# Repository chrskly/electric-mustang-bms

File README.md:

# Electric Mustang BMS

This repo contains the hardware design and software for the custom BMS for my EV conversion project.

## Overview

The BMS is always on.

The battery is made up of one or two BMW PHEV battery packs.

Each battery pack has a positive and negative contactor which are activated by
either the ignition key or when charging.

The BMS is able to inhibit the closing of the contactors in each battery pack
individually.

The car will also have precharge and main contactors in the HVJB. These are
controlled by the inverter.

## Compiling/Installing

### Building the BMS code

```
cd src/build
cmake ../
make
```

### Building the test framework code

```
cd test/build
cmake ../
make
```

## High Voltage wiring

```
       +--------- fuse --- batt1-pos-cont ---+
       |                                     |
       |     +--- fuse --- batt2-pos-cont ---+
       |     |                               |
       |     |                               +--- precharge ---+
batt1 ---   --- batt2                        |                 |
       -     -                               +--- main-cont ---+--->
       |     |
       |     |
       |     +------------ batt2-neg-cont ---+---- neg-cont ------->
       |                                     |
       +------------------ batt1-neg-cont ---+
```

* batt1-pos-cont, batt1-neg-cont, batt2-pos-cont, and batt2-neg-cont are
  contactors located inside the respective battery boxes. They are powered by
  ignition on or by charging on.
* The power for the battery contactors passes through the normally closed side
  of a relay. The BMS can inhibit the closing of the contactors in either
  battery separately by closing the respective relay.
* The inverter controls the precharge, main and neg contactors.

## State machine

### States

* standby
* drive
* batteryHeating
* charging
* batteryEmpty
* overTempFault
* illegalStateTransitionFault
* criticalFault

### Events

| Event | Description |
| --- | --- |
| E_TOO_HOT | The battery is overheating. |
| E_TOO_COLD_TO_CHARGE | The battery temperature is too cold. |
| E_TEMPERATURE_OK | The battery temperature is in an OK range. |
| E_BATTERY_EMPTY | The battery has one or more 'empty' cells. |
| E_BATTERY_NOT_EMPTY | The battery charge is in an OK range. |
| E_BATTERY_FULL | The battery has one or more 'full' cells. |
| E_PACKS_IMBALANCED | The voltage of the two packs differ. |
| E_PACKS_NOT_IMBALANCED | The voltage of the two packs are the same. |
| E_IGNITION_ON | the ignition has been turned on. |
| E_IGNITION_OFF | the ignition has been turned off. |
| E_CHARGING_INITIATED | charging has been initiated. |
| E_CHARGING_TERMINATED | charging has been stopped. |
| E_MODULE_UNRESPONSIVE | One or battery modules are not reporting in to the BMS. |
| E_MODULES_ALL_RESPONSIVE | All battery modules are reporting in to the BMS. |
| E_SHUNT_UNRESPONSIVE | The ISA shunt is not transmitting updates. |
| E_SHUNT_RESPONSIVE | The ISA shunt is transmitting updates. |
| E_DEAD_CELL | On of the cells has failed (voltage too low) |

## Functionality

### General
* Monitor voltage of every cell in the pack.
* Provide SoC estimate (based on shunt data)
* Provide range estimate [TODO]

### Charging
* Provide max charge current value based on temperature and SoC
* Protect cells by disallowing charging at high/low temperatures
* Disallow charging when battery is full

### Driving
* Protect cells by disallowing driving at high temperatures
* Disallow driving when battery is empty

### Paralleling packs

I will be using two BMW PHEV packs connected in parallel. This introduces some
additional complications.

#### Packs Getting Out of Sync

When the car is off, the packs will be disconnected from each other as well as
from the rest of the car. There is the possibility that the packs will drift a
little apart from each other in terms of their voltage. For example, they'll be
placed in different locations in the car, so will experience slightly different
thermals.

* Provide protection for issues relating to paralleling packs. Deny contactor
  close when pack voltages (not cell voltages) differ by more than a certain
  number of mV. Instead, when going into drive mode, only close the
  contactors for the pack with the highest voltage and, when going into charge
  mode, only close the contactors for the pack with the lowest voltage. Car
  will still be drivable and full battery capacity will still be usable (by
  turning ignition off and on again).
* When driving on a subset of packs, allow contactors to close when the pack
  voltages get back into alignment.
* When charging on a subset of packs, allow contactors to close when the pack
  voltages get back into alignment.

#### Dead Cell Detection

One of the risks associated with paralleling packs is if a cell in one of the
packs fails in a closed state, then the voltage of that pack drops. You'll then
get a large, uncontrolled current flow from the 'good' pack to the 'bad' pack.

To attempt to guard against this, this BMS implements dead cell detection. If
any cell is found to have a voltage reading under DEAD_CELL_VOLTAGE that pack is
uncontitionally isolated by inhibiting contactor close (opening the contactors)
for the pack.

If we only have one pack:
  > Warn that dead cell has been detected, but take no other action

If we have multiple packs:
  Idle

### ISA Shunt
* Read CAN messages from shunt to track of voltage, current, kwh
* Reset shunt counters when battery has been charged to 100%

## Connections

1. CAN port connected to main CAN bus.
2. CAN port connected to front battery CAN bus.
3. CAN port connected to rear battery CAN bus.
4. Low side switch for front battery contactors. Contactors are actually
   controlled by inverter, but BMS can override.
5. Low side switch for rear battery contactors. Contactors are actually
   controlled by inverter, but BMS can override.
6. Low side switch to turn on battery heater.
7. IGNITION_ON input signal
8. CHARGE_ENABLE input signal
9. CHARGE_INHIBIT output signal
10. DRIVE_INHIBIT output signal

## Pinout

```
|                                               |
| A7 A8 A9 A10 A11 A12     B1  B2  B3  B4 B5 B6 |
| A6 A5 A4 A3  A2  A1      B12 B11 B10 B9 B8 B7 |
+-----------------------------------------------+
```

### BMS

- A1  : GPIO_13 : IN_3  / BATT1_CONTACTOR_FEEDBACK
- A2  : GPIO_11 : IN_1  / POS_CONTACTOR_FEEDBACK
- A3  : GPIO_9  : IN_X  / CHARGE_ENABLE_IN
- A4  : GPIO_6  : OUT_3 / DRIVE_INHIBIT
- A5  : GPIO_4  : OUT_1 / CHARGE_INHIBIT
- A6  : GPIO_3  : OUT_X / BATT_2_INHIBIT
- A7  : GPIO_2  : OUT_X / BATT_1_INHIBIT
- A8  : GPIO_5  : OUT_2 / HEATER_ENABLE
- A9  : GPIO_7  : OUT_4
- A10 : GPIO_10 : IN_X  / IGNITION_ON_IN
- A11 : GPIO_12 : IN_2  / NEG_CONTACTOR_FEEDBACK
- A12 : GPIO_14 : IN_4  / BATT2_CONTACTOR_FEEDBACK

- B1 : BATT_2_CAN_H
- B2 : BATT_1_CAN_H
- B3 : MAIN_CAN_H
- B4 : GND
- B5 : 12V
- B6 : GND
- B7 : 5V
- B8 : 5V
- B9 : GND
- B10 : MAIN_CAN_L
- B11 : BATT_1_CAN_L
- B12 : BATT_2_CAN_L

### Tester

- A1  : GPIO_13 : IN_3  / DRIVE_INHIBIT
- A2  : GPIO_11 : IN_1  / CHARGE_INHIBIT
- A3  : GPIO_9  : IN_X  / HEATER_ENABLE
- A4  : GPIO_6  : OUT_3 / 
- A5  : GPIO_4  : OUT_1 / CHARGE_ENABLE
- A6  : GPIO_3  : OUT_X / 
- A7  : GPIO_2  : OUT_X / IGNITION_ON
- A8  : GPIO_5  : OUT_2 / 
- A9  : GPIO_7  : OUT_4 /
- A10 : GPIO_10 : IN_X  / 
- A11 : GPIO_12 : IN_2  / BATT_2_INHIBIT
- A12 : GPIO_14 : IN_4  / BATT_1_INHIBIT

- B1 : BATT_2_CAN_H
- B2 : BATT_1_CAN_H
- B3 : MAIN_CAN_H
- B4 : GND
- B5 : 12V
- B6 : GND
- B7 : 5V
- B8 : 5V
- B9 : GND
- B10 : MAIN_CAN_L
- B11 : BATT_1_CAN_L
- B12 : BATT_2_CAN_L

## CAN messages consumed by BMS

- Shunt messages - kWh, Ah, current, voltage (0x521 - 0x528)

## CAN messages produced by BMS

- Shunt reset message
- Min battery voltage (0x351)
- Max battery voltage (0x351)
- Max charge current (0x351)
- Max discharge current (0x351) [ not implemented yet ]
- BMS state - standby, drive, ... (0x352)
- Errors flags - internalError, packsImbalanced, shuntIsDead, illegalStateTransition (0x352)
- Status flags - inhibitCharge, inhibitDrive, heaterEnabled, ignitionOn, chargeEnable, disableRegen (0x352)
- Charge inhibit reason - none, too hot, too cold, battery full, battery empty, charging, illegal state transition (0x352)
- Drive inhibit reason - as above (0x352)
- Welding bits - posContactorWelded, negContactorWelded, batt1ContactorWelded, batt2ContactorWelded (0x352)
- Module liveness (0x353)
- SoC (0x355)
- Battery voltage - as reported by BMS and as reported by shunt (0x356)
- Battery current - as reported by shunt (0x356)
- Battery highest temperature (0x356)
- High cell voltage alarm, warn (0x35A)
- Low cell voltage alarm, warn (0x35A)
- High temp alarm, warn (0x35A)
- Low temp alarm, warn (0x35A) [ not implemented yet ]
- Cell delta alarm (0x35A)

## Configurables

1. minCellVoltage - disallow drive when cell voltage at or below this level.
2. maxCellVoltage - disallow charge when cell voltage at or above this level.
3. maxPackVoltageDelta - max allowed difference in voltage between packs. Above
   this, contactors will not be allowed to close.
4. minChargeTemp - disallow charging at or below this temperature.

## Charging

When in charge mode the BMS will emit a maximum allowed charge current in the
0x351 CAN message. The chargers will listen for this and adjust their request
accordingly.

### Temperature derating

There is a minimum temperature below which we must not charge. So we disallow
charging at or below -10°C.

Above the minimum, we need to limit the charge current. So we ramp up the
allowed current as temperature increases. This is between -10°C and 15°C.

In the 'happy temperature' range (between 15°C and 35°C) we allow the full 125A
(delivered by a 50kw charger). However, if the temperature of the pack increases
by more than 1°C per minute, derate the charge current by 10% for every degree
over.

Above 35°C, we ramp back down the current. We also derate based on temperature
increase on top of that.

It looks something like this.

```
current
   ^
   |
   |                    /----------------------\
   |                  /                         \
   |                /                            \
   |              /                               \
   |            /                                  \
   |          /                                     \
   |        /                                        \
   |      /                                           \
   |    /                                              \
   |  /                                                 \
   +-+------------------+---------------------+----------+----> temperature
    -10°               15°C                  35°C       40°C
```

### SoC derating

TODO : just go slow about 80%?

## Welded Contactor Detection

There are four inputs on the BMS for welded contactor detection.

1. HVJB positive contactor
2. HVJB negative contactor
3. Battery 1 contactors
4. Battery 2 contactors

There are four bits in the status CAN message (0x352) for reporting
welded contactors (one bit for each of the above).

The weld detection only runs when the car is in standby mode (the
only time it makes sense).

Both the positive and negative contactors in the HVJB have dedicated
feedback inputs. The switched side of the auxiliary side of the
contactor should be fed into this input. I.e., feed it 12V when the
contactor is closed.

The battery contactors just have one input each. We can use diodes to
report if either of the battery contactors (positive or negative) are
welded.

## To Do

- [x] Fetch SoC from shunt and store in memory
- [x] Broadcast BMS mode
- [x] CHARGE_ENABLE input
- [x] IGNITION_ON input
- [x] DRIVE_INHIBIT output
- [ ] Use other core for comms?
- [x] Implement balancing
- [x] Implement watchdog
- [ ] On startup, properly detect the state we should start in and immediately switch to that state
- [x] Emulate SimpBMS output CAN messages
- [x] Reset ISA Shunt when battery charged to 100%
- [x] ISA shunt heartbeat
- [x] Warn/alarm flags
- [x] Warn when modules are missing
- [ ] Deal with scenario when one pack is full and one pack is empty
- [x] Communication error bit(s)
- [x] Counter for failed CAN messages received (checksum?), sent
- [x] enable/disable regen bit
- [x] inhibit function naming confusing
- [x] charge_inhibit_reason can msg
- [x] drive_inhibit_reason can msg
- [x] transmit module liveness over can   
- [x] welded contactor detection
- [ ] manual battery pre-heat
- [x] Disallow charging when BMS cannot 'see' shunt
- [ ] Provide range estimate
- [ ] Save certain values to flash (error counters, state?, )
- [ ] Dead cell detection

## Credits

This project uses the [adamczykpiotr/pico-mcp2515](https://github.com/adamczykpiotr/pico-mcp2515) 
library for CAN communication.

The [Tom-evnut/BMWPhevBMS](https://github.com/Tom-evnut/BMWPhevBMS) project was
used as a reference for how to communicate with this battery pack.

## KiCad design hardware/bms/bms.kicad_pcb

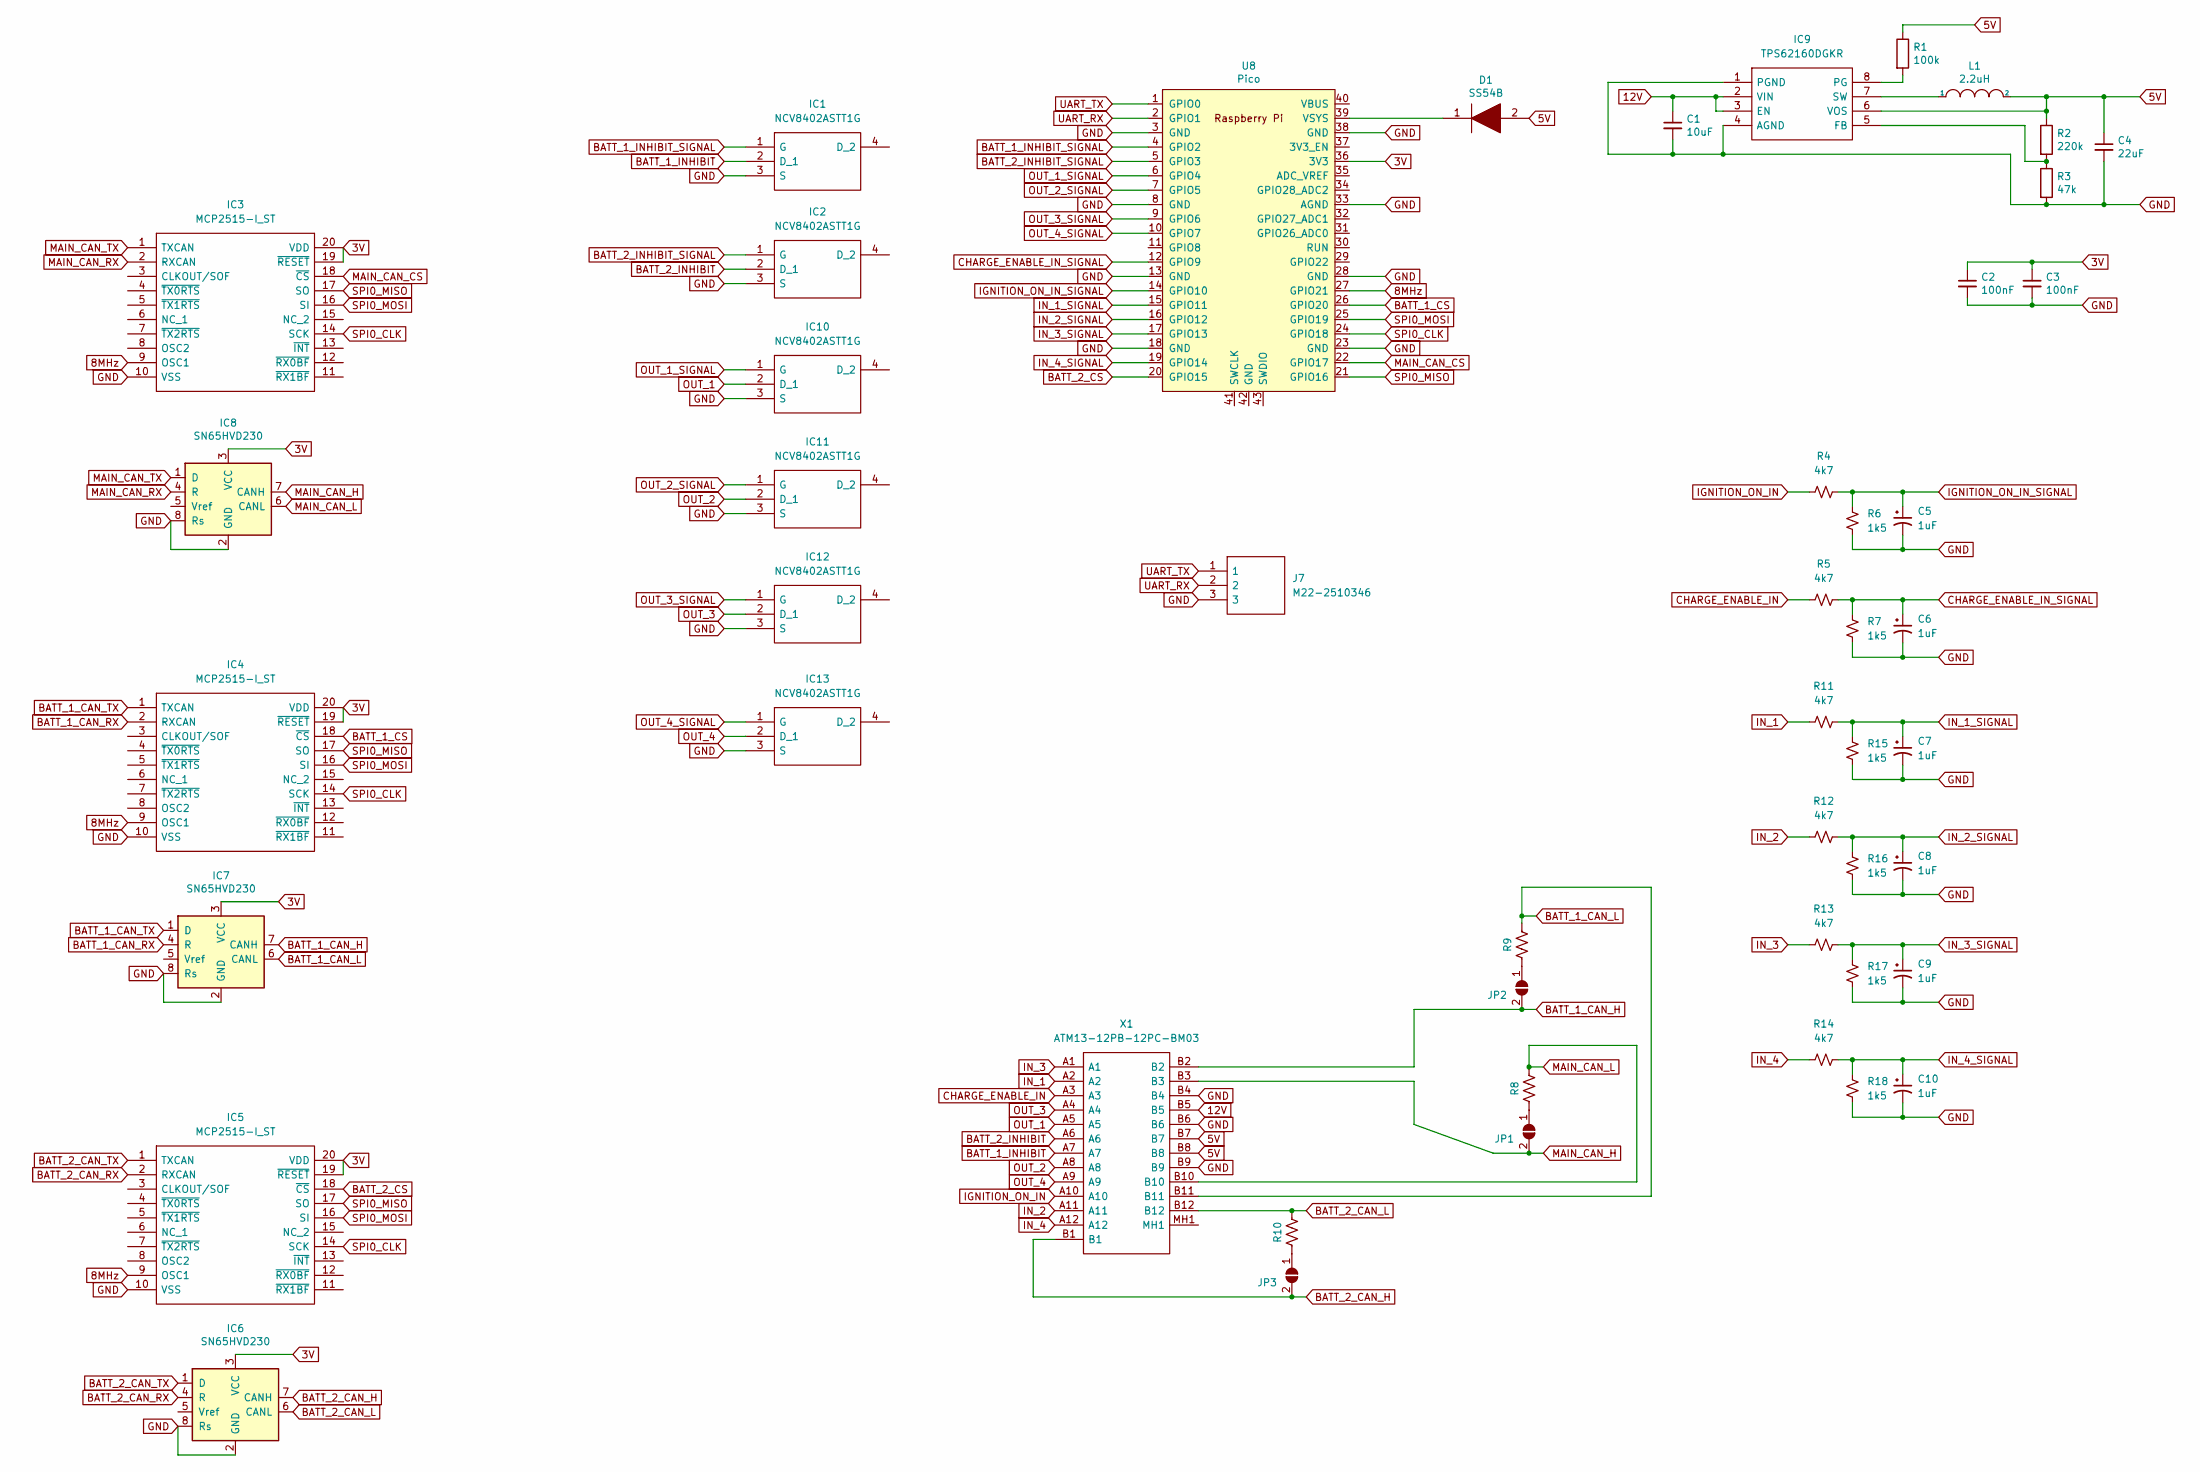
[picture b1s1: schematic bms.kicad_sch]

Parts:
C1: 10uF; C_0603_1608Metric
C2, C3: 100nF; C_0603_1608Metric
C4: 22uF; C_0805_2012Metric
C5, C6, C7, C8, C9, C10: 1uF; C_0603_1608Metric
D1: SS54B; DIOM5336X244N; Manufacturer_Part_Number SS54B
IC1, IC2, IC10, IC11, IC12, IC13: NCV8402ASTT1G; SOT230P700X175-4N; Manufacturer_Part_Number NCV8402ASTT1G; Mouser Part Number 863-NCV8402ASTT1G
IC3, IC4, IC5: MCP2515-I_ST; SOP65P640X120-20N; Manufacturer_Part_Number MCP2515-I/ST
IC6, IC7, IC8: SN65HVD230; SOIC-8_3.9x4.9mm_P1.27mm
IC9: TPS62160DGKR; SOP65P490X110-8N; Manufacturer_Part_Number TPS62160DGKR; Mouser Part Number 595-TPS62160DGKR
J7: M22-2510346; PinHeader_1x03_P2.54mm_Vertical; Manufacturer_Part_Number M22-2510346; Mouser Part Number 855-M22-2510346
JP1, JP2, JP3: SolderJumper_2_Open; SolderJumper-2_P1.3mm_Open_Pad1.0x1.5mm
L1: 2.2uH; NR6028T220M
R1: 100k; R_0805_2012Metric
R2: 220k; R_0805_2012Metric
R3: 47k; R_0805_2012Metric
R4, R5, R11, R12, R13, R14: 4k7; R_0805_2012Metric
R6, R7, R15, R16, R17, R18: 1k5; R_0805_2012Metric
R8, R9, R10: 120; R_0805_2012Metric
U8: Pico; RPi_Pico_SMD_TH
X1: ATM13-12PB-12PC-BM03; ATM1312PB12PCBM03; Manufacturer_Part_Number ATM13-12PB-12PC-BM03; Mouser Part Number 654-ATM1312B12PCBM03

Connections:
3V: C2.1, C3.1, IC3.19 (~RESET), IC3.20 (VDD), IC4.19 (~RESET), IC4.20 (VDD), IC5.19 (~RESET), IC5.20 (VDD), IC6.3 (VCC), IC7.3 (VCC), IC8.3 (VCC), U8.36 (3V3)
5V: C4.1, D1.2, IC9.6 (VOS), L1.2, R1.1, R2.1, X1.B7, X1.B8
8MHz: IC3.9 (OSC1), IC4.9 (OSC1), IC5.9 (OSC1), U8.27 (GPIO21)
12V: C1.1, IC9.2 (VIN), IC9.3 (EN), X1.B5
BATT_1_CAN_H: IC7.7 (CANH), JP2.2 (B), X1.B2
BATT_1_CAN_L: IC7.6 (CANL), R9.1, X1.B11
BATT_1_CAN_RX: IC4.2 (RXCAN), IC7.4 (R)
BATT_1_CAN_TX: IC4.1 (TXCAN), IC7.1 (D)
BATT_1_CS: IC4.18 (~CS), U8.26 (GPIO20)
BATT_1_INHIBIT: IC1.2 (D_1), X1.A7
BATT_1_INHIBIT_SIGNAL: IC1.1 (G), U8.4 (GPIO2)
BATT_2_CAN_H: IC6.7 (CANH), JP3.2 (B), X1.B1
BATT_2_CAN_L: IC6.6 (CANL), R10.1, X1.B12
BATT_2_CAN_RX: IC5.2 (RXCAN), IC6.4 (R)
BATT_2_CAN_TX: IC5.1 (TXCAN), IC6.1 (D)
BATT_2_CS: IC5.18 (~CS), U8.20 (GPIO15)
BATT_2_INHIBIT: IC2.2 (D_1), X1.A6
BATT_2_INHIBIT_SIGNAL: IC2.1 (G), U8.5 (GPIO3)
CHARGE_ENABLE_IN: R5.1, X1.A3
CHARGE_ENABLE_IN_SIGNAL: C6.1, R5.2, R7.1, U8.12 (GPIO9)
GND: C1.2, C2.2, C3.2, C4.2, C5.2, C6.2, C7.2, C8.2, C9.2, C10.2, IC1.3 (S), IC2.3 (S), IC3.10 (VSS), IC4.10 (VSS), IC5.10 (VSS), IC6.2 (GND), IC6.8 (Rs), IC7.2 (GND), IC7.8 (Rs), IC8.2 (GND), IC8.8 (Rs), IC9.1 (PGND), IC9.4 (AGND), IC10.3 (S), IC11.3 (S), IC12.3 (S), IC13.3 (S), J7.3, R3.2, R6.2, R7.2, R15.2, R16.2, R17.2, R18.2, U8.3 (GND), U8.8 (GND), U8.13 (GND), U8.18 (GND), U8.23 (GND), U8.28 (GND), U8.33 (AGND), U8.38 (GND), X1.B4, X1.B6, X1.B9
IGNITION_ON_IN: R4.1, X1.A10
IGNITION_ON_IN_SIGNAL: C5.1, R4.2, R6.1, U8.14 (GPIO10)
IN_1: R11.1, X1.A2
IN_1_SIGNAL: C7.1, R11.2, R15.1, U8.15 (GPIO11)
IN_2: R12.1, X1.A11
IN_2_SIGNAL: C8.1, R12.2, R16.1, U8.16 (GPIO12)
IN_3: R13.1, X1.A1
IN_3_SIGNAL: C9.1, R13.2, R17.1, U8.17 (GPIO13)
IN_4: R14.1, X1.A12
IN_4_SIGNAL: C10.1, R14.2, R18.1, U8.19 (GPIO14)
MAIN_CAN_CS: IC3.18 (~CS), U8.22 (GPIO17)
MAIN_CAN_H: IC8.7 (CANH), JP1.2 (B), X1.B3
MAIN_CAN_L: IC8.6 (CANL), R8.1, X1.B10
MAIN_CAN_RX: IC3.2 (RXCAN), IC8.4 (R)
MAIN_CAN_TX: IC3.1 (TXCAN), IC8.1 (D)
unnamed: D1.1, U8.39 (VSYS)
unnamed: IC9.5 (FB), R2.2, R3.1
unnamed: IC9.7 (SW), L1.1
unnamed: IC9.8 (PG), R1.2
unnamed: JP1.1 (A), R8.2
unnamed: JP2.1 (A), R9.2
unnamed: JP3.1 (A), R10.2
OUT_1: IC10.2 (D_1), X1.A5
OUT_1_SIGNAL: IC10.1 (G), U8.6 (GPIO4)
OUT_2: IC11.2 (D_1), X1.A8
OUT_2_SIGNAL: IC11.1 (G), U8.7 (GPIO5)
OUT_3: IC12.2 (D_1), X1.A4
OUT_3_SIGNAL: IC12.1 (G), U8.9 (GPIO6)
OUT_4: IC13.2 (D_1), X1.A9
OUT_4_SIGNAL: IC13.1 (G), U8.10 (GPIO7)
SPI0_CLK: IC3.14 (SCK), IC4.14 (SCK), IC5.14 (SCK), U8.24 (GPIO18)
SPI0_MISO: IC3.17 (SO), IC4.17 (SO), IC5.17 (SO), U8.21 (GPIO16)
SPI0_MOSI: IC3.16 (SI), IC4.16 (SI), IC5.16 (SI), U8.25 (GPIO19)
UART_RX: J7.2, U8.2 (GPIO1)
UART_TX: J7.1, U8.1 (GPIO0)

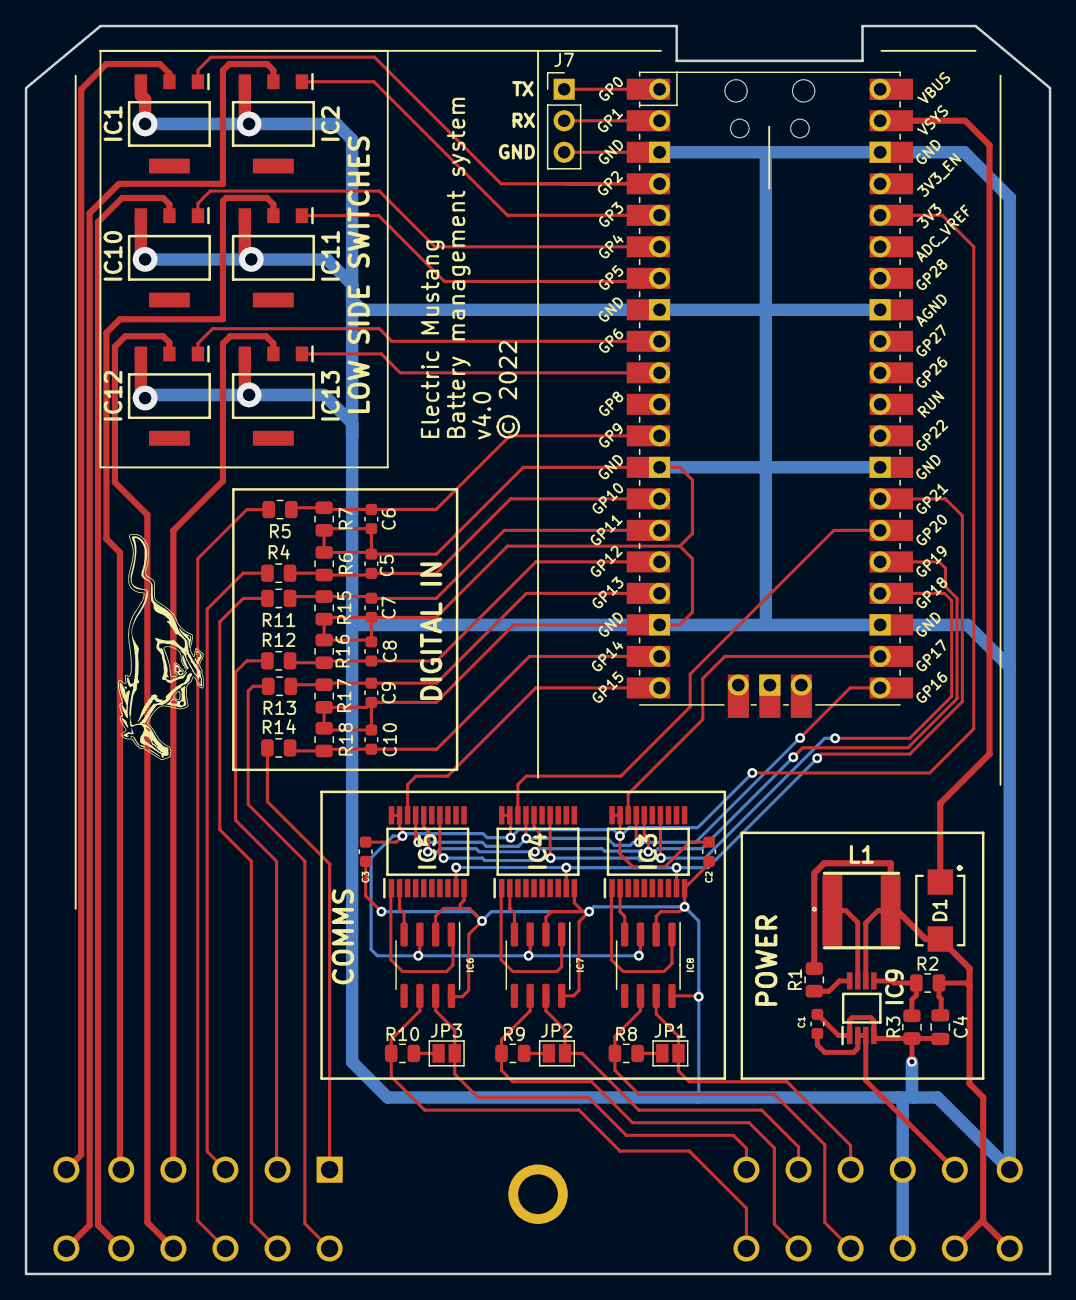
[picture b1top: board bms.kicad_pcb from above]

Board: 2 copper layers, 82.6 x 100.6 mm, 49 parts (0 on the bottom side), 56 nets.

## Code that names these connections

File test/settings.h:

/*
 * This file is part of the ev mustang bms project.
 *
 * Copyright (C) 2024 Christian Kelly <chrskly@chrskly.com>
 *
 * This program is free software: you can redistribute it and/or modify
 * it under the terms of the GNU General Public License as published by
 * the Free Software Foundation, either version 3 of the License, or
 * (at your option) any later version.
 *
 * This program is distributed in the hope that it will be useful,
 * but WITHOUT ANY WARRANTY; without even the implied warranty of
 * MERCHANTABILITY or FITNESS FOR A PARTICULAR PURPOSE.  See the
 * GNU General Public License for more details.
 *
 * You should have received a copy of the GNU General Public License
 * along with this program.  If not, see <http://www.gnu.org/licenses/>.
 */

#ifndef BMS_SRC_SETTINGS_H_
#define BMS_SRC_SETTINGS_H_

#define VERSION 1.0

// Serial port
#define UART_ID      uart0
#define BAUD_RATE   115200
#define UART_TX_PIN      0  // pin 1
#define UART_RX_PIN      1  // pin 2

// CAN bus
#define SPI_PORT      spi0
#define SPI_MISO        16          // pin 21
#define SPI_CLK         18          // pin 24
#define SPI_MOSI        19          // pin 25
#define CAN_CLK_PIN     21          // pin 27
#define MAIN_CAN_CS     17          // pin 22
const int CS_PINS[2] = { 20, 15 };  // Chip select pins for the CAN controllers for each battery pack.

// Inputs
#define DRIVE_INHIBIT_PIN  13                      //
//const bool DRIVE_INHIBIT_ACTIVE_LOW = true;       // Is the drive inhibit signal active low?
#define CHARGE_INHIBIT_PIN 11                      //
//const bool CHARGE_INHIBIT_ACTIVE_LOW = true;      // Is the charge inhibit signal active low?
#define HEATER_ENABLE_PIN   9                      //
//const bool HEATER_ENABLE_ACTIVE_LOW = true;       // Is the heater signal active low?
const int INHIBIT_CONTACTOR_PINS[2] = { 14, 12 };  //
//const bool INHIBIT_CONTACTOR_ACTIVE_LOW = true;   // Is the inhibit contactor signal active low?

// Outputs
#define IGNITION_ENABLE_PIN  2  //
//const bool IGNITION_ENABLE_ACTIVE_LOW = true;  // Is the ignition signal active low?
#define CHARGE_ENABLE_PIN    4  //
//const bool CHARGE_ENABLE_ACTIVE_LOW = true;    // Is the charge signal active low?
#define IN_1_PIN            11  // unused
#define IN_2_PIN            12  // unused
#define IN_3_PIN            13  // unused
#define IN_4_PIN            14  // unused


#define NUM_PACKS         2                        // The total number of paralleled packs in this battery
#define CELLS_PER_MODULE 16                        // The number of cells in each module
#define TEMPS_PER_MODULE  4                        // The number of temperature sensors in each module
#define MODULES_PER_PACK  6                        // The number of modules in each pack

#define PACK_ALIVE_TIMEOUT 5                       // If we have not seen an update from the BMS in
                                                   // PACK_ALIVE_TIMEOUT seconds, then mark the pack
                                                   // as dead.

#define MODULE_TTL 5                               // If we have not seen an update from a module in
                                                   // MODULE_TTL seconds, them mark the module as
                                                   // dead.

#define SHUNT_TTL 3                                // If we have not seen an update from the ISA
                                                   // shunt in SHUNT_TTL seconds, then mark it as
                                                   // dead.

#define SAFE_VOLTAGE_DELTA_BETWEEN_PACKS 0.01      // When closing contactors, the voltage difference between the packs shall not
                                                   // be greater than this voltage, in volts.


// The capacity of the battery pack
#define BATTERY_CAPACITY_WH 14800         // 7.4kWh usable per pack, x2 packs
#define BATTERY_CAPACITY_AS 187200        // 26Ah per pack (93,600 As), x2 packs
#define CALCULATE_SOC_FROM_AMP_SECONDS 1  // Should we calculate SoC from amp seconds (value = 1) or
                                          // kWh (value = 0)? 

// Official min pack voltage = 269V. 269 / 6 / 16 = 2.8020833333V
#define CELL_EMPTY_VOLTAGE 2850

// Official max pack voltage = 398V. 398 / 6 / 16 = 4.1458333333V
#define CELL_FULL_VOLTAGE 4100

#define MINIMUM_TEMPERATURE -20          // 
#define MINIMUM_CHARGING_TEMPERATURE 0   // Disallow charging below this temperature
#define WARNING_TEMPERATURE 30           // 
#define MAXIMUM_TEMPERATURE 50           // Stop everything if the battery is above this temperature

#define CHARGE_THROTTLE_TEMP_LOW  20                // Start throttling charge current when battery sensors above this temperature
#define CHARGE_THROTTLE_TEMP_HIGH 30                // Top of the throttling scale. Limit current to CHARGE_CURRENT_MIN at and above this temperature
#define CHARGE_CURRENT_MAX 125                      // ~50kw
#define CHARGE_CURRENT_MIN 8                        // ~3.3kw

#define BALANCE_INTERVAL 1200                       // number of seconds between balancing sessions

#define CAN_MUTEX_TIMEOUT_MS 1000                   // Timeout for the CAN mutex
#define SEND_FRAME_RETRIES 6                        // Number of times to retry sending a CAN frame
#define READ_FRAME_RETRIES 3

//// ---- CAN message IDs

#define BMS_LIMITS_MSG_ID 0x351                     // Charge/discharge limits message
#define BMS_SOC_MSG_ID 0x355                        // SoC status message
#define BMS_STATUS_MSG_ID 0x356                     // Status message emitted by the BMS
#define BMS_ALARM_MSG_ID 0x35A                      // Warning message emitted by the BMS

#define CAN_ID_ISA_SHUNT_AH 0x527                   // Message ISA shunt sends which contains Ah data.
#define CAN_ID_ISA_SHUNT_WH 0x528                   // Message ISA shunt sends which contains Wh data.

#endif  // BMS_SRC_SETTINGS_H_

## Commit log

2024-02-29 Split out from other repo
2024-03-02 Docs update
2024-03-03 Add get_clock() from chademo project
2024-03-03 Add module heartbeat. Move module polling under battery.c. Add BMS status CAN message.
2024-03-03 docs
2024-03-10 Rename variable to make it a bit more understandable
2024-03-10 Add heartbeat for ISA shunt
2024-03-10 Early flagging of too cold to charge
2024-03-24 Restructure
2024-03-27 start doing some safety/sanity checks and report this as a status bit in the BMS status msg. Reorganise some of the temperature thresholds
2024-03-29 Add status bit to BMS status message to indicate when packs are imbalanced
2024-03-29 Split module liveness and state bits into separate messages
2024-04-07 Update copyright date
2024-04-07 unused
2024-04-13 some work on testing code
2024-04-14 Start tracking pico_sdk_import.cmake
2024-04-14 more work on testing rig
2024-04-20 Watchdog numbers the wrong way around
2024-04-20 Store voltages in mV because that's how we're getting from the BMS
2024-04-20 Fix format for sending mock cell voltages
2024-04-20 gitignore
2024-04-20 Print state on serial console
2024-04-20 Get temp readings working right
2024-04-20 Transmit mock temperature data
2024-04-20 Forgot these files in last commit
2024-04-23 Rename README
2024-04-23 backup update
2024-04-23 Build file
2024-04-24 Fleshing out the test framework some more
2024-04-24 minor tweaks
2024-04-27 Add input handling for CHARGE_INHIBIT and DRIVE_INHIBIT
2024-04-27 Flesh out first two test cases
2024-04-27 Fix data types
2024-04-28 small state correction
2024-04-28 start dealing with the 1xx test cases
2024-05-04 Work on test case 102 and 103
2024-05-04 typo, we can only get out of illegalStateTransitionFault when both ignition and charge are off
2024-05-04 Implement 1xx and 2xx test cases
2024-05-04 State machine, better handling of bad transitions
2024-05-04 Better fn name
2024-05-04 Get rid of EMERGENCY_SHUTDOWN stuff
2024-05-04 docs change
2024-05-19 Fairly major restructuring. Add in separate class for dealing with shunt. Move some functionality into more appropriate class homes
2024-05-19 Fiddling with tests
2024-05-19 Remove unused files
2024-05-20 Fix bms.set_state
2024-05-20 Using wrong pin
2024-05-26 Fix up charge/drive inhibit logic
2024-05-26 Working getting test case 002 to pass
2024-06-23 More major restructuring
2024-06-24 Finally got all three CAN ports working. Many of the test cases are now passing.
2024-06-24 hardware backup
2024-06-24 tidy up
2024-06-24 Fix test case 101
2024-07-07 Count the number of times we get invalid events in the state machine. Also work on the logic of the state machine a bit
2024-07-07 Add xor checksum to bms frames
2024-07-13 Add temperature derating for charging.
2024-07-14 Add safeties to statemachine and rework a bit
2024-07-14 Add charge inhibit reason
2024-07-14 Add drive inhibit reason
2024-07-16 Fix fn naming confusion
2024-07-16 old archive
2024-07-16 add archive
2024-07-16 Add vscode stuff
2024-07-16 Add disableRegen bit to can msg
2024-07-16 Add module liveness check to CAN msg
2024-07-22 Add welded contactor detection
2024-07-28 Read in actual states of GPIO on startup
2024-07-28 Set temp at start of test 001 in case we've come from a test which sets overtemp
2024-07-28 make pass/fail easier to read
2024-07-28 Infinite loop and total wonkiness in module liveness
2024-07-28 Only report on heater/enable when changing state
2024-07-28 Not allowing contactors to close when packs imbalanced going into charge mode
2024-07-28 Fix up full/empty battery tests
2024-07-28 Deal with equalised packs when charging
2024-10-12 Rework 0xx test cases. Add a couple more empty/full tests. Refactor.
2024-12-26 typo
2025-01-03 Fold InhibitReason into drive_inhibit and charge_inhibit functions to make statemachine easier to read
2025-01-07 Split max charge current into by_temp and by_soc
2025-01-07 Make test case comments uniform. Add some more tests
2025-01-07 small docs update
2025-01-19 Rework statemaching logic
2025-01-21 Missing battery full health check
2025-01-21 tiny docs update
2025-01-21 Fix reporting of state in CAN messages
2025-01-21 Send module liveness bit in CAN msg
2025-01-21 Send invalidEventCounter in CAN status msg
2025-01-21 Tidy up unused states
2025-01-27 Make error messages a little clearer
2025-01-27 Missing criticalFault when setting light blink pattern
2025-01-27 Set driveInhibitReason to a sane initial value
2025-01-27 Get rid of commented out code. Disable test message sending on startup.
2025-01-27 hardware backups
2025-01-27 whitespace
2025-01-27 Remove commented out fn
2025-02-01 Keep track of CAN errors in sending messages to modules
2025-02-01 Fix capitalisation
2025-02-01 Simplify this bit for now
2025-02-01 Add error counters for rx/tx on main CAN bus
2025-02-01 Add counters for tx/rx on main CAN bus
2025-02-01 Take a stab at adding cell balancing
2025-02-02 Don't bother setting CAN ids in settings, just define directly in code
2025-02-02 Cleanup settings
2025-02-02 Move charge current calculation in to generic timer so we have it all the time. Move SoC calculation here too.
2025-02-16 Missing some includes
2025-02-16 Missing another include
2025-02-16 Take inhibitited pack into account when calculating max charge current
2025-02-16 tiny bit for formatting
2025-02-16 formatting
2025-02-22 Flesh out 0x35A msg a bit. Use Victron format.
2025-09-07 CHARGE_INHIBIT can be on in charging state
2025-09-07 Make logging in io more consistent
2025-09-08 Work on test cases
2025-09-08 Update testing docs
2025-11-10 Some work on dead cell detection
2025-11-10 bup update

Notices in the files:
hardware/bms/bms.kicad_pcb:
© 2022
